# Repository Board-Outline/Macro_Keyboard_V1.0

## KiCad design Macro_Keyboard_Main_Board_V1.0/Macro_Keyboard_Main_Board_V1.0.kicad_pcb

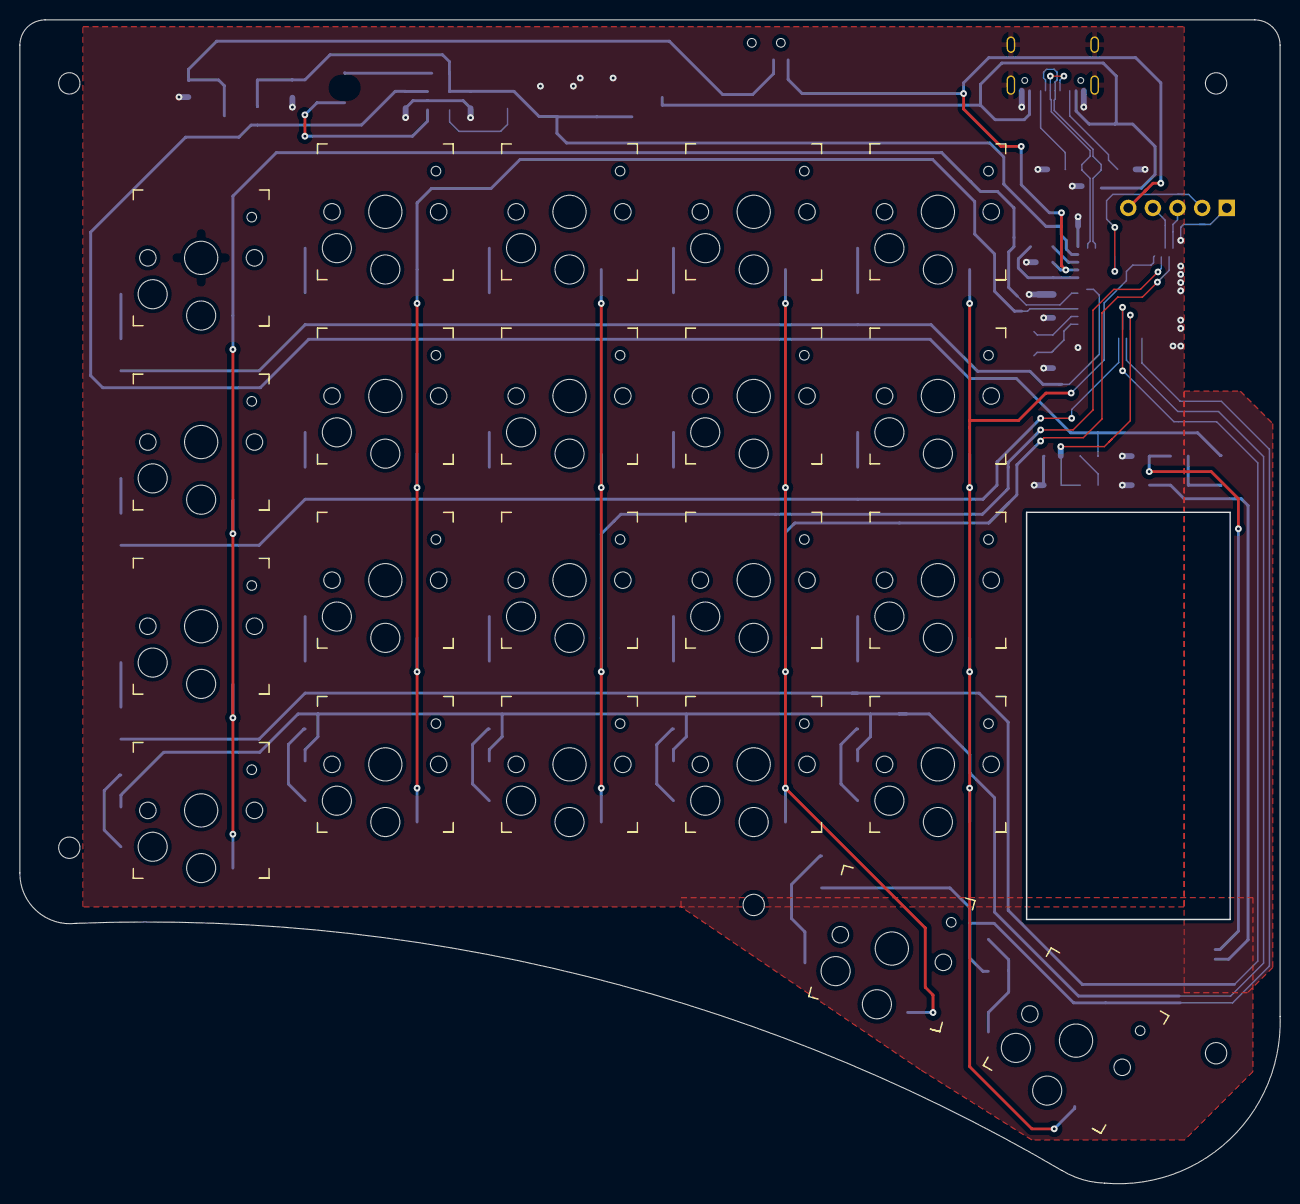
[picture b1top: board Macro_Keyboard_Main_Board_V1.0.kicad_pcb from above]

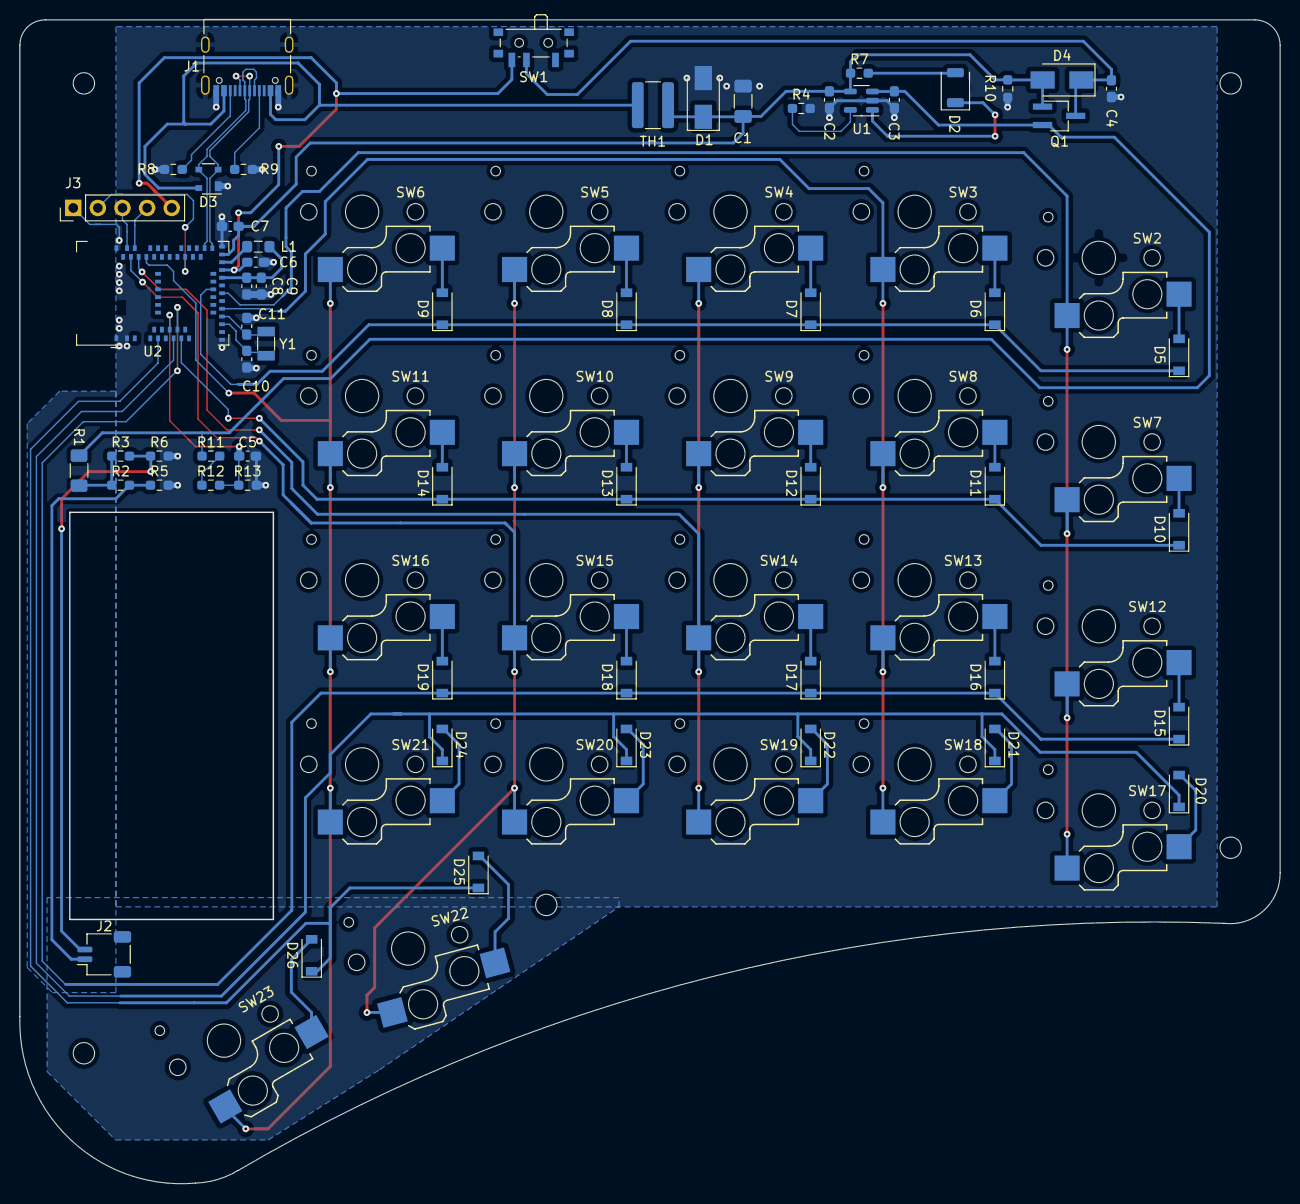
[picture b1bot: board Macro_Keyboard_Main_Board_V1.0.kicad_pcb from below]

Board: 2 copper layers, 130.0 x 120.0 mm, 87 parts (60 on the bottom side), 57 nets.

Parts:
C1: 10uF; C_1206_3216Metric_Pad1.33x1.80mm_HandSolder
C2, C3, C4, C6, C7, C9: 4u7F; C_0603_1608Metric_Pad1.08x0.95mm_HandSolder
C5: 10nF; C_0603_1608Metric_Pad1.08x0.95mm_HandSolder
C8: 1uF; C_0603_1608Metric_Pad1.08x0.95mm_HandSolder
C10, C11: 15pF; C_0603_1608Metric_Pad1.08x0.95mm_HandSolder
D1: SMAJ5.0A; D_SMA
D2: LED; LED_1206_3216Metric_ReverseMount_Hole1.8x2.4mm
D3: PRTR5V0U2X; SOT-143
D4: B160-E3; D_SMA
D5, D6, D7, D8, D9, D10, D11, D12, D13, D14, D15, D16, D17, D18, D19, D20, D21, D22, D23, D24, D25, D26: 1N4148W; D_SOD-123
H1, H2, H3, H4, H5: MountingHole M2; MountingHole_2.2mm_M2_ISO14580
J1: USB_C_Receptacle_USB2.0; USB_C_Receptacle_Palconn_UTC16-G
J2: JST SM02B-SRSS-TB(LF)(SN); JST_SH_SM02B-SRSS-TB_1x02-1MP_P1.00mm_Horizontal
J3: Conn_01x05; PinHeader_1x05_P2.54mm_Vertical
L1: 10uH; L_0805_2012Metric_Pad1.05x1.20mm_HandSolder
Q1: DMG2301L-7; TSOT-23_HandSoldering
R1: 0R; R_1206_3216Metric_Pad1.30x1.75mm_HandSolder
R2, R6, R7: N.F.; R_0603_1608Metric_Pad0.98x0.95mm_HandSolder
R3, R5: 0R; R_0603_1608Metric_Pad0.98x0.95mm_HandSolder
R4: 20K; R_0603_1608Metric_Pad0.98x0.95mm_HandSolder
R8, R9: 5K1; R_0603_1608Metric_Pad0.98x0.95mm_HandSolder
R10: 10K; R_0603_1608Metric_Pad0.98x0.95mm_HandSolder
R11, R12: 2M; R_0603_1608Metric_Pad0.98x0.95mm_HandSolder
R13: 10M; R_0603_1608Metric_Pad0.98x0.95mm_HandSolder
SW1: SW_SPDT PCM12SMTR; SW_SPDT_PCM12
SW2, SW3, SW4, SW5, SW6, SW7, SW8, SW9, SW10, SW11, SW12, SW13, SW14, SW15, SW16, SW17, SW18, SW19, SW20, SW21, SW22, SW23: SW_Push; Kailh_socket_PG1350
TH1: MF-MSMF050-2; R_1218_3246Metric_Pad1.22x4.75mm_HandSolder
U1: MCP73831T-2ACI/OT; SOT-23-5
U2: MDBT50Q-1MV2; Raytac_MDBT50Q
Y1: 32768Hz; Crystal_SMD_3215-2Pin_3.2x1.5mm

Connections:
+BATT: C3.1, Q1.2 (D), R1.1, R11.1, U1.3 (VBAT)
/keyboard/BAT_VOUT: C5.1, R12.2, R13.1, U2.9 (P0.03/AIN1)
/keyboard/CC1: J1.A5 (CC1), R9.1
/keyboard/CC2: J1.B5 (CC2), R8.1
/keyboard/COL1: SW2.1, SW7.1, SW12.1, SW17.1, U2.24 (P0.08)
/keyboard/COL2: SW3.1, SW8.1, SW13.1, SW18.1, U2.20 (P0.04/AIN2)
/keyboard/COL3: SW4.1, SW9.1, SW14.1, SW19.1, U2.50 (P1.02)
/keyboard/COL4: SW5.1, SW10.1, SW15.1, SW20.1, SW22.1, U2.52 (P0.09/NFC1)
/keyboard/COL5: SW6.1, SW11.1, SW16.1, SW21.1, SW23.1, U2.49 (P0.25)
/keyboard/RESET: J3.2, U2.40 (~RESET/P0.18)
/keyboard/ROW1: D5.1 (K), D6.1 (K), D7.1 (K), D8.1 (K), D9.1 (K), U2.25 (P1.08)
/keyboard/ROW2: D10.1 (K), D11.1 (K), D12.1 (K), D13.1 (K), D14.1 (K), U2.12 (P0.31/AIN7)
/keyboard/ROW3: D15.1 (K), D16.1 (K), D17.1 (K), D18.1 (K), D19.1 (K), U2.11 (P0.02/AIN0)
/keyboard/ROW4: D20.1 (K), D21.1 (K), D22.1 (K), D23.1 (K), D24.1 (K), U2.10 (P0.29/AIN5)
/keyboard/ROW5: D25.1 (K), D26.1 (K), U2.6 (P1.13)
/keyboard/SWDCLK: J3.3, U2.53 (SWDCLK)
/keyboard/SWDIO: J3.4, U2.51 (SWDIO)
/keyboard/USB_N: D3.3 (I/O2), J1.A7 (D-), J1.B7 (D-), U2.35 (D+)
/keyboard/USB_P: D3.2 (I/O1), J1.A6 (D+), J1.B6 (D+), U2.34 (D-)
GND: C1.2, C2.2, C3.2, C4.2, C5.2, C6.2, C7.2, C8.2, C9.2, C10.1, C11.1, D1.2 (A), D3.1 (GND), J1.A1 (GND), J1.A12 (GND), J1.B1 (GND), J1.B12 (GND), J1.S1 (SHIELD), J3.1, R4.2, R5.2, R6.2, R8.2, R9.2, R10.2, R13.2, U1.2 (VSS), U2.1 (GND), U2.2 (GND), U2.15 (GND), U2.33 (GND), U2.55 (GND)
unnamed: C4.1, D4.1 (K), Q1.3 (S), SW1.2 (B)
unnamed: C8.1, C9.1, L1.1, U2.28 (VDD)
unnamed: C10.2, U2.17 (XL1/P0.00), Y1.1
unnamed: C11.2, U2.18 (XL2/P0.01), Y1.2
unnamed: D2.1 (K), U1.1 (STAT)
unnamed: D2.2 (A), R7.2
unnamed: D3.4 (VCC), J1.A4 (VBUS), J1.A9 (VBUS), J1.B4 (VBUS), J1.B9 (VBUS), TH1.2
unnamed: D5.2 (A), SW2.2
unnamed: D6.2 (A), SW3.2
unnamed: D7.2 (A), SW4.2
unnamed: D8.2 (A), SW5.2
unnamed: D9.2 (A), SW6.2
unnamed: D10.2 (A), SW7.2
unnamed: D11.2 (A), SW8.2
unnamed: D12.2 (A), SW9.2
unnamed: D13.2 (A), SW10.2
unnamed: D14.2 (A), SW11.2
unnamed: D15.2 (A), SW12.2
unnamed: D16.2 (A), SW13.2
unnamed: D17.2 (A), SW14.2
unnamed: D18.2 (A), SW15.2
unnamed: D19.2 (A), SW16.2
unnamed: D20.2 (A), SW17.2
unnamed: D21.2 (A), SW18.2
unnamed: D22.2 (A), SW19.2
unnamed: D23.2 (A), SW20.2
unnamed: D24.2 (A), SW21.2
unnamed: D25.2 (A), SW22.2
unnamed: D26.2 (A), SW23.2
unnamed: J2.1, R2.2, R5.1
unnamed: J2.2, R3.2, R6.1
unnamed: L1.2, U2.31 (DCCH)
unnamed: R1.2, R2.1, R3.1
unnamed: R4.1, U1.5 (PROG)
unnamed: R11.2, R12.1
VBUS: C1.1, C2.1, C7.1, D1.1 (K), D4.2 (A), Q1.1 (G), R7.1, R10.1, TH1.1, U1.4 (VDD), U2.32 (VBUS)
VDD: C6.1, J3.5, SW1.3 (C), U2.30 (VDDH)

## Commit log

2022-11-24 Initial Comit
2022-11-27 Weekend changes
2022-12-05 Newest Changes Added
2023-09-09 Added notes
